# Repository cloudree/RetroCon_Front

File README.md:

# RetroCon_Front
Front Pack version of RetroCon (MSX2 compatible, VDP is V9958)
* Retrocon is MSX2+ compatible machine made by KevinCho ckevin@hanmail.net

/KiCad : schematics of Kicad

/CPLD : source for ALTERA EPM7128SLC84 CPLD, you must use Altera Quartus 13.0sp1 or below

/tinyFGPA : source for tinyFPGA board (PS/2 Keyboard interface)

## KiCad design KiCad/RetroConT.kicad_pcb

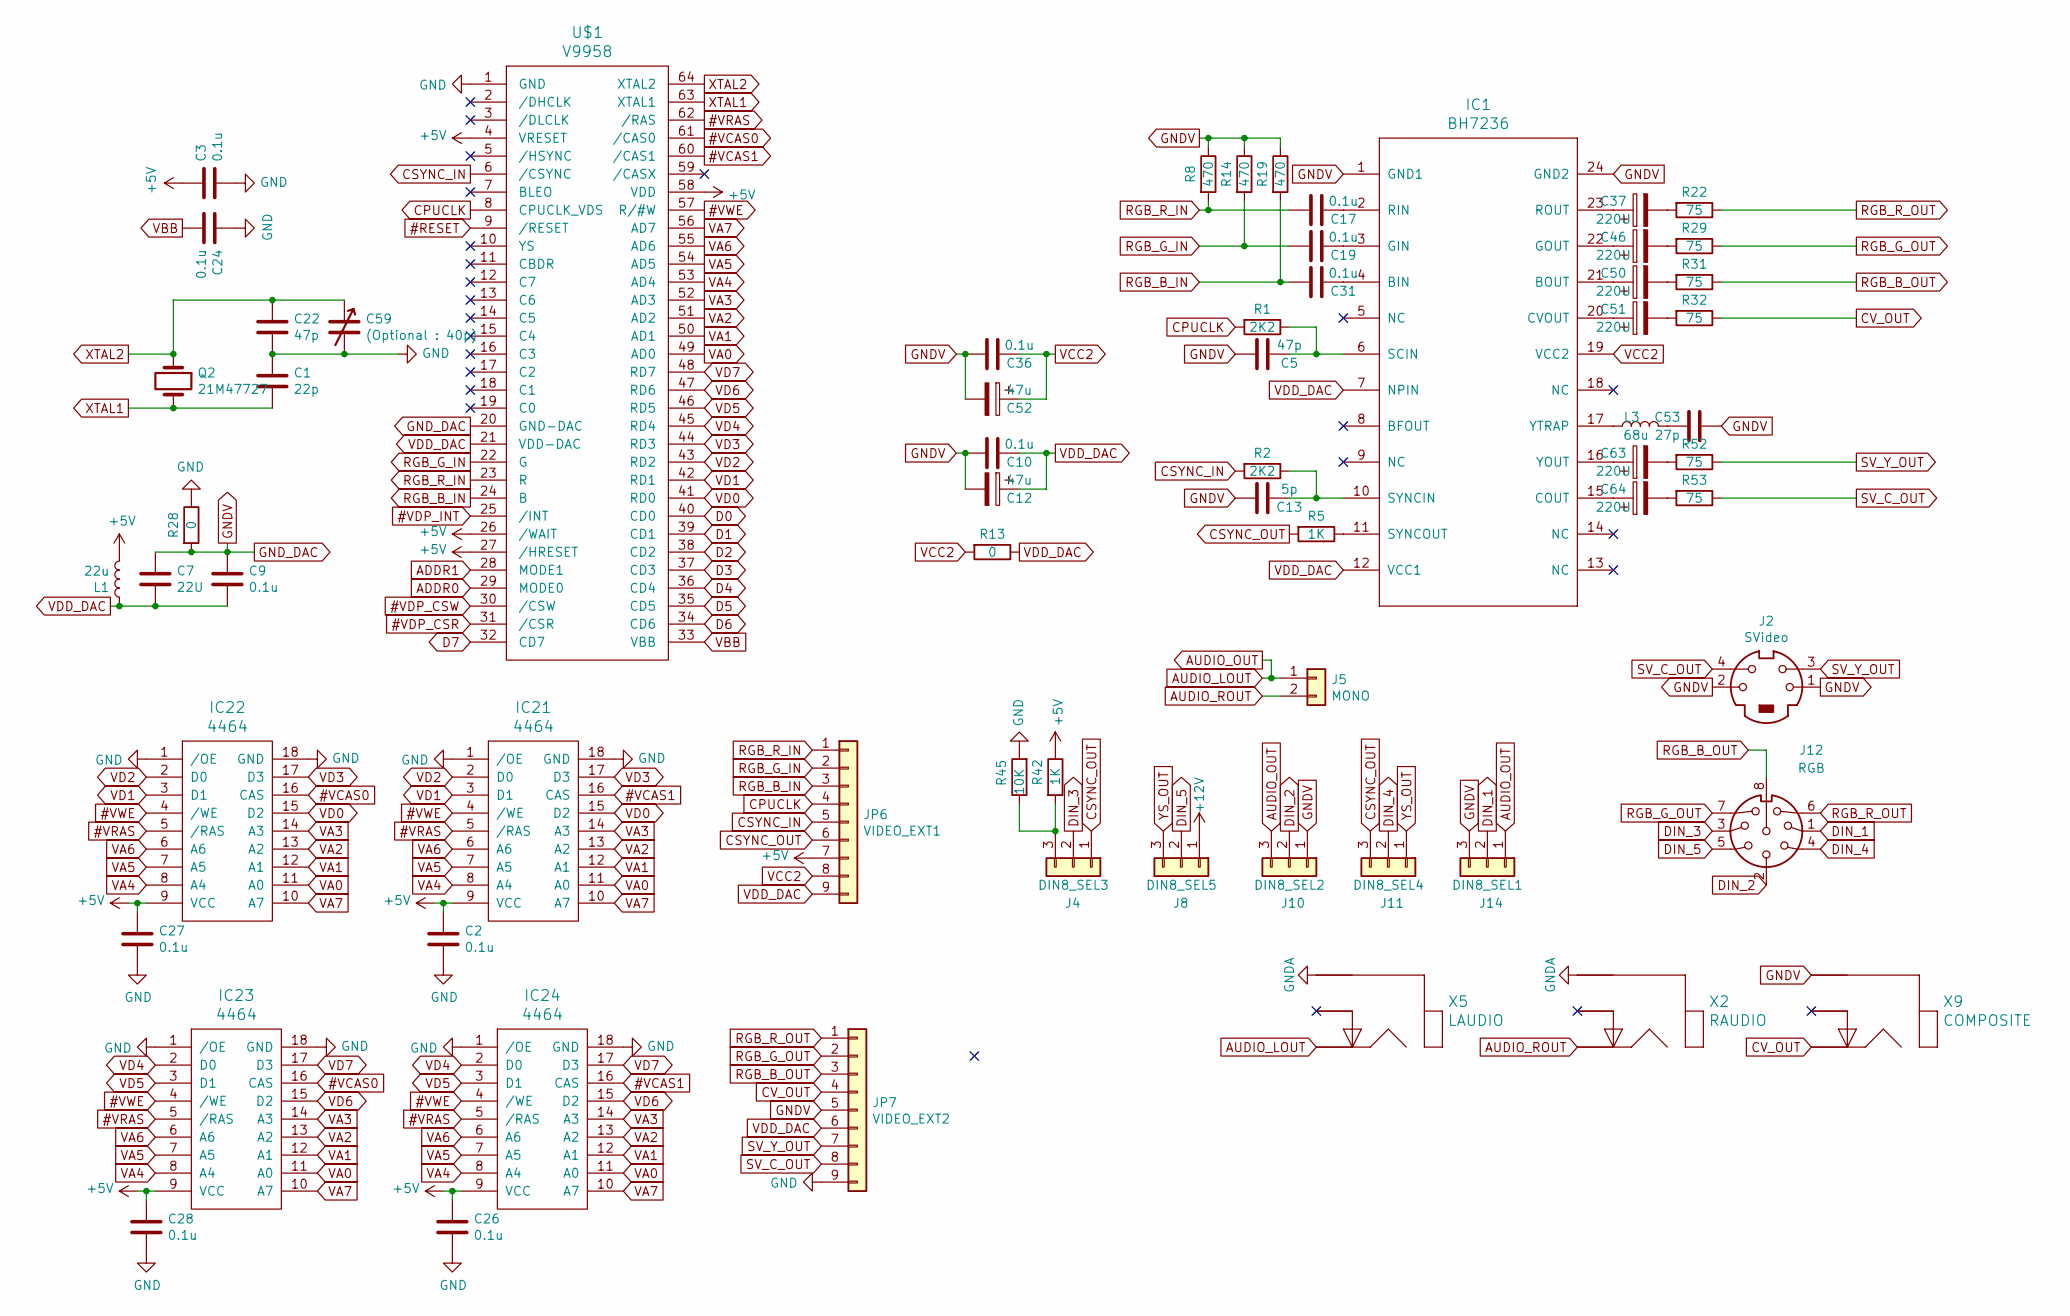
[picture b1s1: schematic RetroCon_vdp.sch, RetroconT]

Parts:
C1: 22p; C_0805_2012Metric_Pad1.15x1.40mm_HandSolder
C2, C3, C9, C10, C17, C19, C24, C26, C27, C28, C31, C36: 0.1u; C_0805_2012Metric_Pad1.15x1.40mm_HandSolder
C5, C22: 47p; C_0805_2012Metric_Pad1.15x1.40mm_HandSolder
C7: 22U; CP_Radial_D6.3mm_P2.50mm
C12, C52: 47u; CP_Radial_D6.3mm_P2.50mm
C13: 5p; C_0805_2012Metric_Pad1.15x1.40mm_HandSolder
C37, C46, C50, C51, C63, C64: 220U; CP_Radial_D6.3mm_P2.50mm
C53: 27p; C_0805_2012Metric_Pad1.15x1.40mm_HandSolder
C59: (Optional : 40p); C_Rect_L7.0mm_W6.5mm_P5.00mm
IC1: BH7236; SOP-24_7.5x15.4mm_P1.27mm
IC21, IC22, IC23, IC24: 4464; DIP-18_W7.62mm_Socket
J2: SVideo; Mini_din4
J4: DIN8_SEL3; PinHeader_1x03_P2.54mm_Vertical
J5: MONO; PinSocket_2x01_P2.54mm_Vertical
J8: DIN8_SEL5; PinHeader_1x03_P2.54mm_Vertical
J10: DIN8_SEL2; PinHeader_1x03_P2.54mm_Vertical
J11: DIN8_SEL4; PinHeader_1x03_P2.54mm_Vertical
J12: RGB; DIN-804_8P
J14: DIN8_SEL1; PinHeader_1x03_P2.54mm_Vertical
JP6: VIDEO_EXT1; PinHeader_1x09_P2.54mm_Vertical
JP7: VIDEO_EXT2; PinHeader_1x09_P2.54mm_Vertical
L1: 22u; L_0805_2012Metric_Pad1.15x1.40mm_HandSolder
L3: 68u; L_0805_2012Metric_Pad1.15x1.40mm_HandSolder
Q2: 21M47727; Crystal_HC49-U_Vertical
R1, R2: 2K2; R_0805_HandSoldering
R5, R42: 1K; R_0805_HandSoldering
R8, R14, R19: 470; R_0805_HandSoldering
R13, R28: 0; R_0805_HandSoldering
R22, R29, R31, R32, R52, R53: 75; R_0805_HandSoldering
R45: 10K; R_0805_HandSoldering
U$1: V9958; SDIP-64
X2: RAUDIO; RCA_102
X5: LAUDIO; RCA_102
X9: COMPOSITE; RCA_102

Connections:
#ExRESET: U$1.9 (/RESET); also elsewhere on the board
#VCAS0: IC22.16 (CAS), IC23.16 (CAS), U$1.61 (/CAS0)
#VCAS1: IC21.16 (CAS), IC24.16 (CAS), U$1.60 (/CAS1)
#VDP_CSR: U$1.31 (/CSR); also elsewhere on the board
#VDP_CSW: U$1.30 (/CSW); also elsewhere on the board
#VDP_INT: U$1.25 (/INT); also elsewhere on the board
#VRAS: IC21.5 (/RAS), IC22.5 (/RAS), IC23.5 (/RAS), IC24.5 (/RAS), U$1.62 (/RAS)
#VWE: IC21.4 (/WE), IC22.4 (/WE), IC23.4 (/WE), IC24.4 (/WE), U$1.57 (R/#W)
+5V: C2.1, C3.1, C26.1, C27.1, C28.1, IC21.9 (VCC), IC22.9 (VCC), IC23.9 (VCC), IC24.9 (VCC), JP6.7, L1.2, R42.1, U$1.4 (VRESET), U$1.26 (/WAIT), U$1.27 (/HRESET), U$1.58 (VDD); also elsewhere on the board
+12V: J8.1; also elsewhere on the board
ADDR0: U$1.29 (MODE0); also elsewhere on the board
ADDR1: U$1.28 (MODE1); also elsewhere on the board
AUDIO_LOUT: J5.1, J10.3, J14.1, X5.2; also elsewhere on the board
AUDIO_ROUT: J5.2, X2.2; also elsewhere on the board
CPUCLK: JP6.4, R1.2, U$1.8 (CPUCLK_VDS); also elsewhere on the board
CSYNC_IN: JP6.5, R2.2, U$1.6 (/CSYNC)
CSYNC_OUT: J4.1, J11.3, JP6.6, R5.2
CV_OUT: JP7.4, R32.1, X9.2
D0: U$1.40 (CD0); also elsewhere on the board
D1: U$1.39 (CD1); also elsewhere on the board
D2: U$1.38 (CD2); also elsewhere on the board
D3: U$1.37 (CD3); also elsewhere on the board
D4: U$1.36 (CD4); also elsewhere on the board
D5: U$1.35 (CD5); also elsewhere on the board
D6: U$1.34 (CD6); also elsewhere on the board
D7: U$1.32 (CD7); also elsewhere on the board
DIN_1: J12.1, J14.2
DIN_2: J10.2, J12.2
DIN_3: J4.2, J12.3
DIN_4: J11.2, J12.4
DIN_5: J8.2, J12.5
GND: C1.1, C2.2, C3.2, C22.2, C24.1, C26.2, C27.2, C28.2, C59.2, IC21.1 (/OE), IC21.18 (GND), IC22.1 (/OE), IC22.18 (GND), IC23.1 (/OE), IC23.18 (GND), IC24.1 (/OE), IC24.18 (GND), JP7.9, R28.1, R45.2, U$1.1 (GND); also elsewhere on the board
GNDA: X2.1, X5.1; also elsewhere on the board
GNDV: C5.2, C7.2, C9.2, C10.2, C12.2, C13.2, C36.2, C52.2, C53.2, IC1.1 (GND1), IC1.24 (GND2), J2.1, J2.2, J10.1, J14.3, JP7.5, R8.1, R14.1, R19.1, R28.2, U$1.20 (GND-DAC), X9.1
unnamed: C5.1, IC1.6 (SCIN), R1.1
unnamed: C13.1, IC1.10 (SYNCIN), R2.1
unnamed: C17.1, IC1.2 (RIN)
unnamed: C19.1, IC1.3 (GIN)
unnamed: C31.1, IC1.4 (BIN)
unnamed: C37.1, IC1.23 (ROUT)
unnamed: C37.2, R22.2
unnamed: C46.1, IC1.22 (GOUT)
unnamed: C46.2, R29.2
unnamed: C50.1, IC1.21 (BOUT)
unnamed: C50.2, R31.2
unnamed: C51.1, IC1.20 (CVOUT)
unnamed: C51.2, R32.2
unnamed: C53.1, L3.2
unnamed: C63.1, IC1.16 (YOUT)
unnamed: C63.2, R52.2
unnamed: C64.1, IC1.15 (COUT)
unnamed: C64.2, R53.2
unnamed: IC1.11 (SYNCOUT), R5.1
unnamed: IC1.17 (YTRAP), L3.1
unnamed: J4.3, R42.2, R45.1
RGB_B_IN: C31.2, JP6.3, R19.2, U$1.24 (B)
RGB_B_OUT: J12.8, JP7.3, R31.1
RGB_G_IN: C19.2, JP6.2, R14.2, U$1.22 (G)
RGB_G_OUT: J12.7, JP7.2, R29.1
RGB_R_IN: C17.2, JP6.1, R8.2, U$1.23 (R)
RGB_R_OUT: J12.6, JP7.1, R22.1
SV_C_OUT: J2.4, JP7.8, R53.1
SV_Y_OUT: J2.3, JP7.7, R52.1
VA0: IC21.11 (A0), IC22.11 (A0), IC23.11 (A0), IC24.11 (A0), U$1.49 (AD0)
VA1: IC21.12 (A1), IC22.12 (A1), IC23.12 (A1), IC24.12 (A1), U$1.50 (AD1)
VA2: IC21.13 (A2), IC22.13 (A2), IC23.13 (A2), IC24.13 (A2), U$1.51 (AD2)
VA3: IC21.14 (A3), IC22.14 (A3), IC23.14 (A3), IC24.14 (A3), U$1.52 (AD3)
VA4: IC21.8 (A4), IC22.8 (A4), IC23.8 (A4), IC24.8 (A4), U$1.53 (AD4)
VA5: IC21.7 (A5), IC22.7 (A5), IC23.7 (A5), IC24.7 (A5), U$1.54 (AD5)
VA6: IC21.6 (A6), IC22.6 (A6), IC23.6 (A6), IC24.6 (A6), U$1.55 (AD6)
VA7: IC21.10 (A7), IC22.10 (A7), IC23.10 (A7), IC24.10 (A7), U$1.56 (AD7)
VBB: C24.2, U$1.33 (VBB)
VCC2: C36.1, C52.1, IC1.19 (VCC2), JP6.8, R13.2
VD0: IC21.15 (D2), IC22.15 (D2), U$1.41 (RD0)
VD1: IC21.3 (D1), IC22.3 (D1), U$1.42 (RD1)
VD2: IC21.2 (D0), IC22.2 (D0), U$1.43 (RD2)
VD3: IC21.17 (D3), IC22.17 (D3), U$1.44 (RD3)
VD4: IC23.2 (D0), IC24.2 (D0), U$1.45 (RD4)
VD5: IC23.3 (D1), IC24.3 (D1), U$1.46 (RD5)
VD6: IC23.15 (D2), IC24.15 (D2), U$1.47 (RD6)
VD7: IC23.17 (D3), IC24.17 (D3), U$1.48 (RD7)
VDD_DAC: C7.1, C9.1, C10.1, C12.1, IC1.7 (NPIN), IC1.12 (VCC1), JP6.9, JP7.6, L1.1, R13.1, U$1.21 (VDD-DAC)
XTAL1: C1.2, Q2.2, U$1.63 (XTAL1)
XTAL2: C22.1, C59.1, Q2.1, U$1.64 (XTAL2)
YS_OUT: J8.3, J11.1

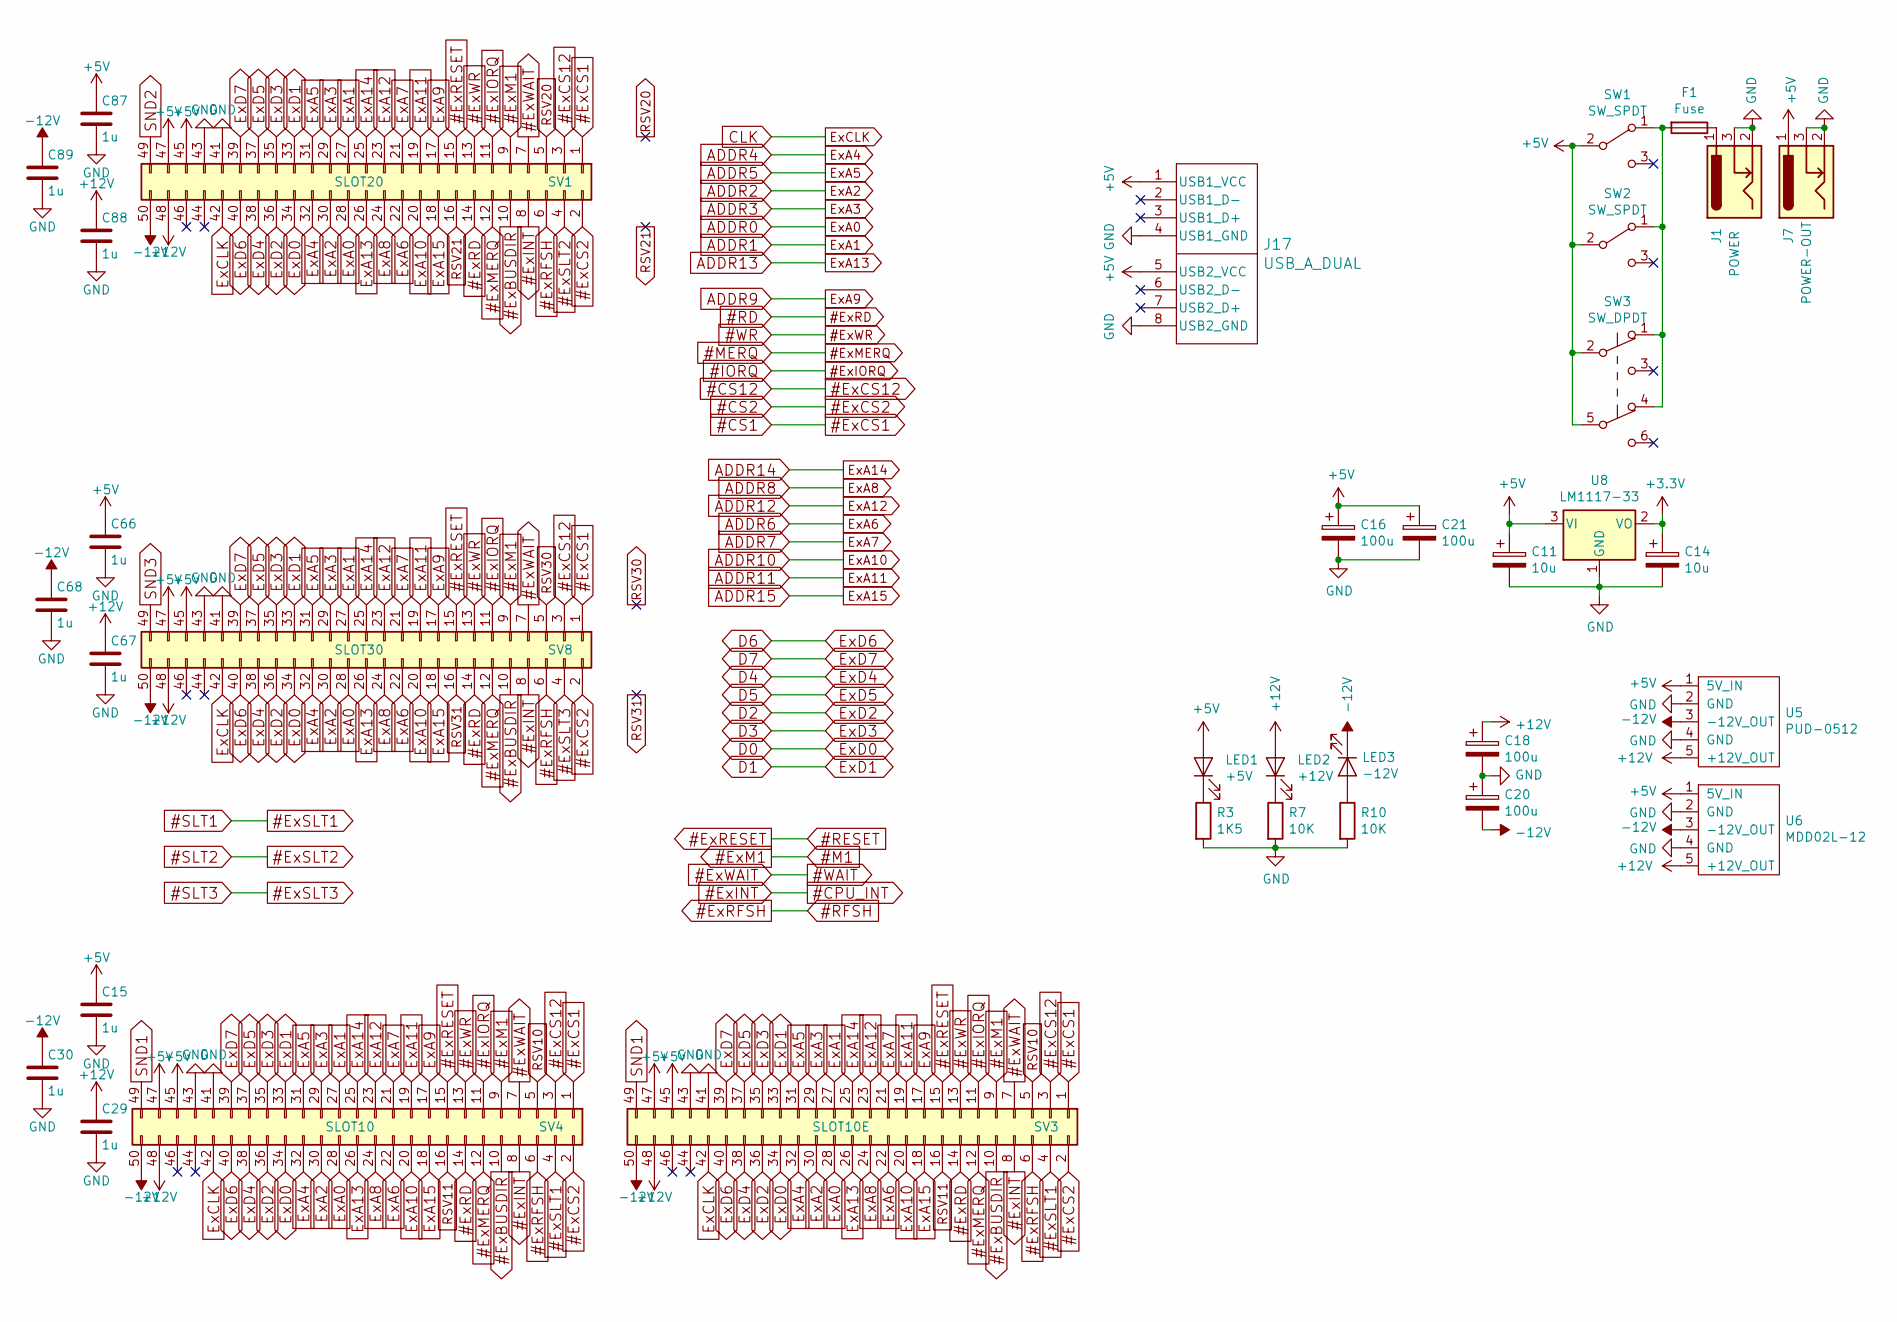
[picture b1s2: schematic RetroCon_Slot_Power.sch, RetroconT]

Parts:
C11, C14: 10u; CP_Radial_D6.3mm_P2.50mm
C15, C29, C30, C66, C67, C68, C87, C88, C89: 1u; C_0805_2012Metric_Pad1.15x1.40mm_HandSolder
C16, C18, C20, C21: 100u; CP_Radial_D6.3mm_P2.50mm
F1: Fuse; Fuse_1812_4532Metric_Pad1.30x3.40mm_HandSolder
J1: POWER; PO-PowerJack
J7: POWER-OUT; PO-PowerJack
J17: USB_A_DUAL
LED1: +5V; LED_0805_2012Metric
LED2: +12V; LED_0805_2012Metric
LED3: -12V; LED_0805_2012Metric
R3: 1K5; R_0805_HandSoldering
R7, R10: 10K; R_0805_HandSoldering
SV1: SLOT20; MSX_Edge_50_Slot
SV3: SLOT10E; MSX_Edge_50_Slot_Conencter
SV4: SLOT10; MSX_Edge_50_Slot
SV8: SLOT30; MSX_Edge_50_Slot_Universal
SW1: SW_SPDT; Switch-Toggle-Mini
SW2: SW_SPDT; MTS-102_Vertical_PCB
SW3: SW_DPDT; SW_DPDT_PS-22E05
U5: PUD-0512
U6: MDD02L-12
U8: LM1117-33; SOT-223-3_TabPin2

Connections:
#CPU_INT: SV1.8, SV3.8, SV4.8, SV8.8; also elsewhere on the board
#CS1: SV1.1, SV3.1, SV4.1, SV8.1; also elsewhere on the board
#CS2: SV1.2, SV3.2, SV4.2, SV8.2; also elsewhere on the board
#CS12: SV1.3, SV3.3, SV4.3, SV8.3; also elsewhere on the board
#ExBUSDIR: SV1.10, SV3.10, SV4.10, SV8.10
#ExIORQ: SV1.11, SV3.11, SV4.11, SV8.11; also elsewhere on the board
#ExM1: SV1.9, SV3.9, SV4.9, SV8.9; also elsewhere on the board
#ExMERQ: SV1.12, SV3.12, SV4.12, SV8.12; also elsewhere on the board
#ExRD: SV1.14, SV3.14, SV4.14, SV8.14; also elsewhere on the board
#ExRESET: SV1.15, SV3.15, SV4.15, SV8.15; also elsewhere on the board
#ExRFSH: SV1.6, SV3.6, SV4.6, SV8.6; also elsewhere on the board
#ExSLT1: SV3.4, SV4.4; also elsewhere on the board
#ExSLT2: SV1.4; also elsewhere on the board
#ExSLT3: SV8.4; also elsewhere on the board
#ExWAIT: SV1.7, SV3.7, SV4.7, SV8.7; also elsewhere on the board
#ExWR: SV1.13, SV3.13, SV4.13, SV8.13; also elsewhere on the board
+3V3: C14.1, U8.2 (VO); also elsewhere on the board
+5V: C11.1, C15.1, C16.1, C21.1, C66.1, C87.1, J7.1, J17.1 (USB1_VCC), J17.5 (USB2_VCC), LED1.2 (A), SV1.45, SV1.47, SV3.45, SV3.47, SV4.45, SV4.47, SV8.45, SV8.47, SW1.2 (B), SW2.2 (B), SW3.2 (B), SW3.5 (B), U5.1 (5V_IN), U6.1 (5V_IN), U8.3 (VI); also elsewhere on the board
+12V: C18.1, C29.1, C67.1, C88.1, LED2.2 (A), SV1.48, SV3.48, SV4.48, SV8.48, U5.5 (+12V_OUT), U6.5 (+12V_OUT); also elsewhere on the board
-12V: C20.2, C30.1, C68.1, C89.1, LED3.1 (K), SV1.50, SV3.50, SV4.50, SV8.50, U5.3 (-12V_OUT), U6.3 (-12V_OUT); also elsewhere on the board
ADDR0: SV1.28, SV3.28, SV4.28, SV8.28; also elsewhere on the board
ADDR1: SV1.27, SV3.27, SV4.27, SV8.27; also elsewhere on the board
ADDR2: SV1.30, SV3.30, SV4.30, SV8.30; also elsewhere on the board
ADDR3: SV1.29, SV3.29, SV4.29, SV8.29; also elsewhere on the board
ADDR4: SV1.32, SV3.32, SV4.32, SV8.32; also elsewhere on the board
ADDR5: SV1.31, SV3.31, SV4.31, SV8.31; also elsewhere on the board
ADDR6: SV1.22, SV3.22, SV4.22, SV8.22; also elsewhere on the board
ADDR7: SV1.21, SV3.21, SV4.21, SV8.21; also elsewhere on the board
ADDR8: SV1.24, SV3.24, SV4.24, SV8.24; also elsewhere on the board
ADDR9: SV1.17, SV3.17, SV4.17, SV8.17; also elsewhere on the board
ADDR10: SV1.20, SV3.20, SV4.20, SV8.20; also elsewhere on the board
ADDR11: SV1.19, SV3.19, SV4.19, SV8.19; also elsewhere on the board
ADDR12: SV1.23, SV3.23, SV4.23, SV8.23; also elsewhere on the board
ADDR13: SV1.26, SV3.26, SV4.26, SV8.26; also elsewhere on the board
ADDR14: SV1.25, SV3.25, SV4.25, SV8.25; also elsewhere on the board
ADDR15: SV1.18, SV3.18, SV4.18, SV8.18; also elsewhere on the board
CLK: SV1.42, SV3.42, SV4.42, SV8.42; also elsewhere on the board
D0: SV1.34, SV3.34, SV4.34, SV8.34; also elsewhere on the board
D1: SV1.33, SV3.33, SV4.33, SV8.33; also elsewhere on the board
D2: SV1.36, SV3.36, SV4.36, SV8.36; also elsewhere on the board
D3: SV1.35, SV3.35, SV4.35, SV8.35; also elsewhere on the board
D4: SV1.38, SV3.38, SV4.38, SV8.38; also elsewhere on the board
D5: SV1.37, SV3.37, SV4.37, SV8.37; also elsewhere on the board
D6: SV1.40, SV3.40, SV4.40, SV8.40; also elsewhere on the board
D7: SV1.39, SV3.39, SV4.39, SV8.39; also elsewhere on the board
GND: C11.2, C14.2, C15.2, C16.2, C18.2, C20.1, C21.2, C29.2, C30.2, C66.2, C67.2, C68.2, C87.2, C88.2, C89.2, J1.2, J1.3, J7.2, J7.3, J17.4 (USB1_GND), J17.8 (USB2_GND), R3.2, R7.2, R10.2, SV1.41, SV1.43, SV3.41, SV3.43, SV4.41, SV4.43, SV8.41, SV8.43, U5.2 (GND), U5.4 (GND), U6.2 (GND), U6.4 (GND), U8.1 (GND); also elsewhere on the board
unnamed: F1.1, J1.1
unnamed: F1.2, SW1.1 (A), SW2.1 (A), SW3.1 (A), SW3.4 (A)
unnamed: LED1.1 (K), R3.1
unnamed: LED2.1 (K), R7.1
unnamed: LED3.2 (A), R10.1
RSV10: SV3.5, SV4.5
RSV11: SV3.16, SV4.16
RSV20: SV1.5
RSV21: SV1.16
RSV30: SV8.5
RSV31: SV8.16
SND1: SV3.49, SV4.49; also elsewhere on the board
SND2: SV1.49; also elsewhere on the board
SND3: SV8.49; also elsewhere on the board

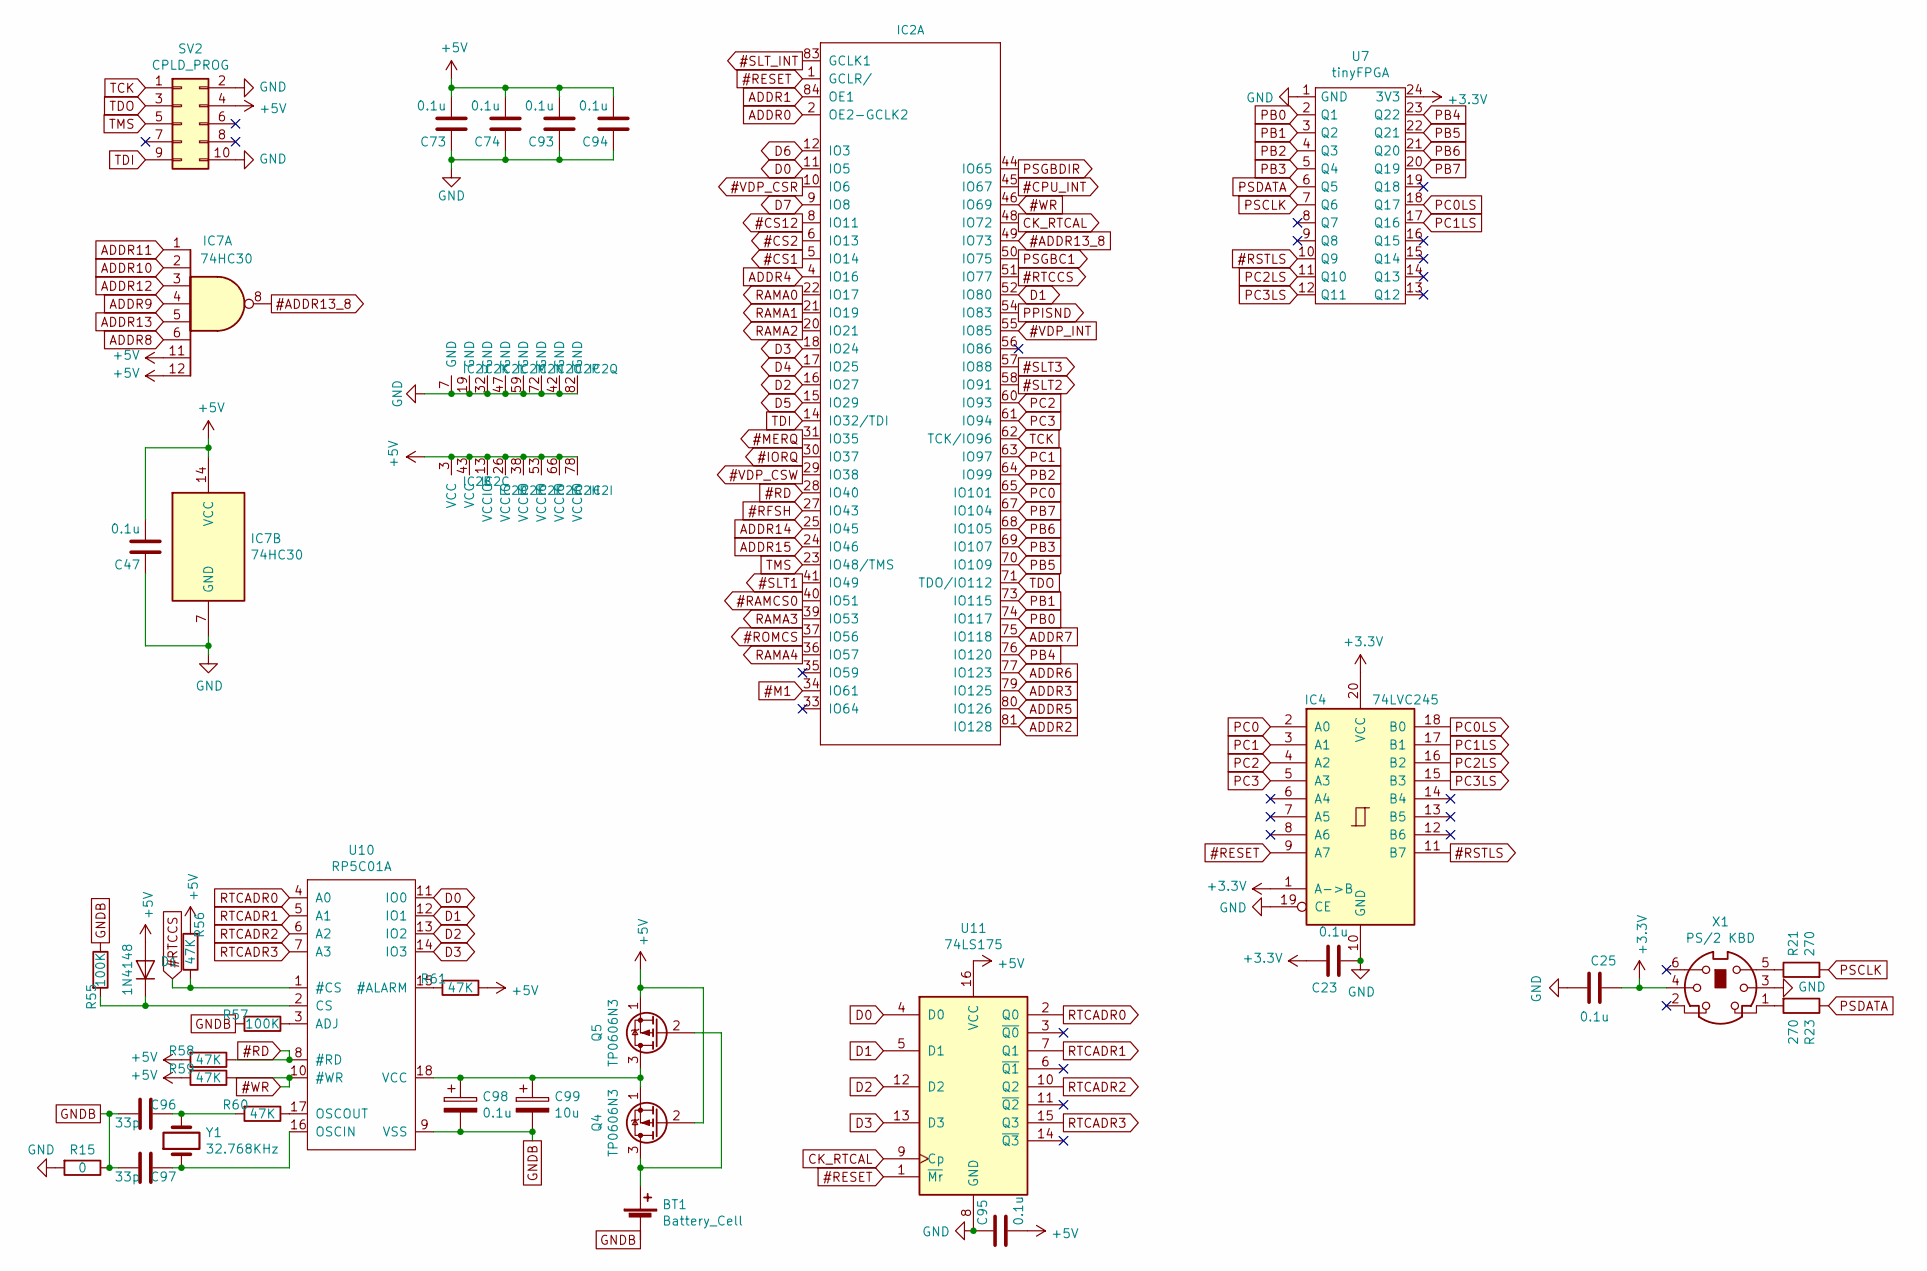
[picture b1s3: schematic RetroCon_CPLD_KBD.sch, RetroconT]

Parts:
BT1: Battery_Cell; BatteryHolder_Keystone_104_1x23mm
C23, C25, C47, C73, C74, C93, C94, C95, C98: 0.1u; C_0805_2012Metric_Pad1.15x1.40mm_HandSolder
C96, C97: 33p; C_0805_2012Metric_Pad1.15x1.40mm_HandSolder
C99: 10u; CP_Radial_D6.3mm_P2.50mm
D1: 1N4148; D_0805_2012Metric_Pad1.15x1.40mm_HandSolder
IC2: EPM7128-J84SOC-RetroCon-eagle-import; PLCC-84_THT-Socket
IC4: 74LVC245; DIP-20_W7.62mm_Socket
IC7: 74HC30; SOIC-14_3.9x8.7mm_P1.27mm
Q4, Q5: TP0606N3; TO-92_Inline
R15: 0; R_0805_HandSoldering
R21, R23: 270; R_0805_HandSoldering
R55, R57: 100K; R_0805_HandSoldering
R56, R58, R59, R60, R61: 47K; R_0805_HandSoldering
SV2: CPLD_PROG; PinHeader_2x05_P2.54mm_Vertical
U7: tinyFPGA; DIP-24_W15.24mm
U10: RP5C01A; DIP-18_W7.62mm_Socket
U11: 74LS175; SOIC-16_3.9x9.9mm_P1.27mm
X1: PS/2 KBD; Mini_din6
Y1: 32.768KHz; Crystal_DS26_D2.0mm_L6.0mm_Vertical

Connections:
#ADDR13_8: IC2.49 (IO73), IC7.8
#CPU_INT: IC2.45 (IO67); also elsewhere on the board
#CS1: IC2.5 (IO14); also elsewhere on the board
#CS2: IC2.6 (IO13); also elsewhere on the board
#CS12: IC2.8 (IO11); also elsewhere on the board
#ExIORQ: IC2.30 (IO37); also elsewhere on the board
#ExM1: IC2.34 (IO61); also elsewhere on the board
#ExMERQ: IC2.31 (IO35); also elsewhere on the board
#ExRD: IC2.28 (IO40), R58.1, U10.8 (#RD); also elsewhere on the board
#ExRESET: IC2.1 (GCLR/), IC4.9 (A7), U11.1 (~Mr); also elsewhere on the board
#ExRFSH: IC2.27 (IO43); also elsewhere on the board
#ExSLT1: IC2.41 (IO49); also elsewhere on the board
#ExSLT2: IC2.58 (IO91); also elsewhere on the board
#ExSLT3: IC2.57 (IO88); also elsewhere on the board
#ExWR: IC2.46 (IO69), R59.1, U10.10 (#WR); also elsewhere on the board
#RAMCS0: IC2.40 (IO51); also elsewhere on the board
#ROMCS: IC2.37 (IO56); also elsewhere on the board
#RSTLS: IC4.11 (B7), U7.10 (Q9)
#RTCCS: IC2.51 (IO77), R56.1, U10.1 (#CS)
#SLT_INT: IC2.83 (GCLK1); also elsewhere on the board
#VDP_CSR: IC2.10 (IO6); also elsewhere on the board
#VDP_CSW: IC2.29 (IO38); also elsewhere on the board
#VDP_INT: IC2.55 (IO85); also elsewhere on the board
+3V3: C23.2, C25.2, IC4.1 (A->B), IC4.20 (VCC), U7.24 (3V3), X1.4; also elsewhere on the board
+5V: C47.2, C73.2, C74.2, C93.2, C94.2, C95.2, D1.2 (A), IC2.3 (VCC), IC2.13 (VCCIO), IC2.26 (VCCIO), IC2.38 (VCCIO), IC2.43 (VCC), IC2.53 (VCCIO), IC2.66 (VCCIO), IC2.78 (VCCIO), IC7.11, IC7.12, IC7.14 (VCC), Q4.2 (G), Q5.1 (S), R56.2, R58.2, R59.2, R61.1, SV2.4, U11.16 (VCC); also elsewhere on the board
ADDR0: IC2.2 (OE2-GCLK2); also elsewhere on the board
ADDR1: IC2.84 (OE1); also elsewhere on the board
ADDR2: IC2.81 (IO128); also elsewhere on the board
ADDR3: IC2.79 (IO125); also elsewhere on the board
ADDR4: IC2.4 (IO16); also elsewhere on the board
ADDR5: IC2.80 (IO126); also elsewhere on the board
ADDR6: IC2.77 (IO123); also elsewhere on the board
ADDR7: IC2.75 (IO118); also elsewhere on the board
ADDR8: IC7.6; also elsewhere on the board
ADDR9: IC7.4; also elsewhere on the board
ADDR10: IC7.2; also elsewhere on the board
ADDR11: IC7.1; also elsewhere on the board
ADDR12: IC7.3; also elsewhere on the board
ADDR13: IC7.5; also elsewhere on the board
ADDR14: IC2.25 (IO45); also elsewhere on the board
ADDR15: IC2.24 (IO46); also elsewhere on the board
CK_RTCAL: IC2.48 (IO72), U11.9 (Cp)
D0: IC2.11 (IO5), U10.11 (IO0), U11.4 (D0); also elsewhere on the board
D1: IC2.52 (IO80), U10.12 (IO1), U11.5 (D1); also elsewhere on the board
D2: IC2.16 (IO27), U10.13 (IO2), U11.12 (D2); also elsewhere on the board
D3: IC2.18 (IO24), U10.14 (IO3), U11.13 (D3); also elsewhere on the board
D4: IC2.17 (IO25); also elsewhere on the board
D5: IC2.15 (IO29); also elsewhere on the board
D6: IC2.12 (IO3); also elsewhere on the board
D7: IC2.9 (IO8); also elsewhere on the board
GND: C23.1, C25.1, C47.1, C73.1, C74.1, C93.1, C94.1, C95.1, IC2.7 (GND), IC2.19 (GND), IC2.32 (GND), IC2.42 (GND), IC2.47 (GND), IC2.59 (GND), IC2.72 (GND), IC2.82 (GND), IC4.10 (GND), IC4.19 (CE), IC7.7 (GND), R15.2, SV2.2, SV2.10, U7.1 (GND), U11.8 (GND), X1.3; also elsewhere on the board
GNDB: BT1.2 (-), C96.1, C97.1, C98.2, C99.2, R15.1, R55.1, R57.2, U10.9 (VSS)
unnamed: BT1.1 (+), Q4.3 (D), Q5.2 (G)
unnamed: C96.2, R60.2, Y1.2
unnamed: C97.2, U10.16 (OSCIN), Y1.1
unnamed: C98.1, C99.1, Q4.1 (S), Q5.3 (D), U10.18 (VCC)
unnamed: D1.1 (K), R55.2, U10.2 (CS)
unnamed: R21.1, X1.5
unnamed: R23.2, X1.1
unnamed: R57.1, U10.3 (ADJ)
unnamed: R60.1, U10.17 (OSCOUT)
unnamed: R61.2, U10.15 (#ALARM)
PB0: IC2.74 (IO117), U7.2 (Q1)
PB1: IC2.73 (IO115), U7.3 (Q2)
PB2: IC2.64 (IO99), U7.4 (Q3)
PB3: IC2.69 (IO107), U7.5 (Q4)
PB4: IC2.76 (IO120), U7.23 (Q22)
PB5: IC2.70 (IO109), U7.22 (Q21)
PB6: IC2.68 (IO105), U7.21 (Q20)
PB7: IC2.67 (IO104), U7.20 (Q19)
PC0: IC2.65 (IO101), IC4.2 (A0)
PC0LS: IC4.18 (B0), U7.18 (Q17)
PC1: IC2.63 (IO97), IC4.3 (A1)
PC1LS: IC4.17 (B1), U7.17 (Q16)
PC2: IC2.60 (IO93), IC4.4 (A2)
PC2LS: IC4.16 (B2), U7.11 (Q10)
PC3: IC2.61 (IO94), IC4.5 (A3)
PC3LS: IC4.15 (B3), U7.12 (Q11)
PPISND: IC2.54 (IO83); also elsewhere on the board
PSCLK: R21.2, U7.7 (Q6)
PSDATA: R23.1, U7.6 (Q5)
PSGBC1: IC2.50 (IO75); also elsewhere on the board
PSGBDIR: IC2.44 (IO65); also elsewhere on the board
RAMA0: IC2.22 (IO17); also elsewhere on the board
RAMA1: IC2.21 (IO19); also elsewhere on the board
RAMA2: IC2.20 (IO21); also elsewhere on the board
RAMA3: IC2.39 (IO53); also elsewhere on the board
RAMA4: IC2.36 (IO57); also elsewhere on the board
RTCADR0: U10.4 (A0), U11.2 (Q0)
RTCADR1: U10.5 (A1), U11.7 (Q1)
RTCADR2: U10.6 (A2), U11.10 (Q2)
RTCADR3: U10.7 (A3), U11.15 (Q3)
TCK: IC2.62 (TCK/IO96), SV2.1
TDI: IC2.14 (IO32/TDI), SV2.9
TDO: IC2.71 (TDO/IO112), SV2.3
TMS: IC2.23 (IO48/TMS), SV2.5
